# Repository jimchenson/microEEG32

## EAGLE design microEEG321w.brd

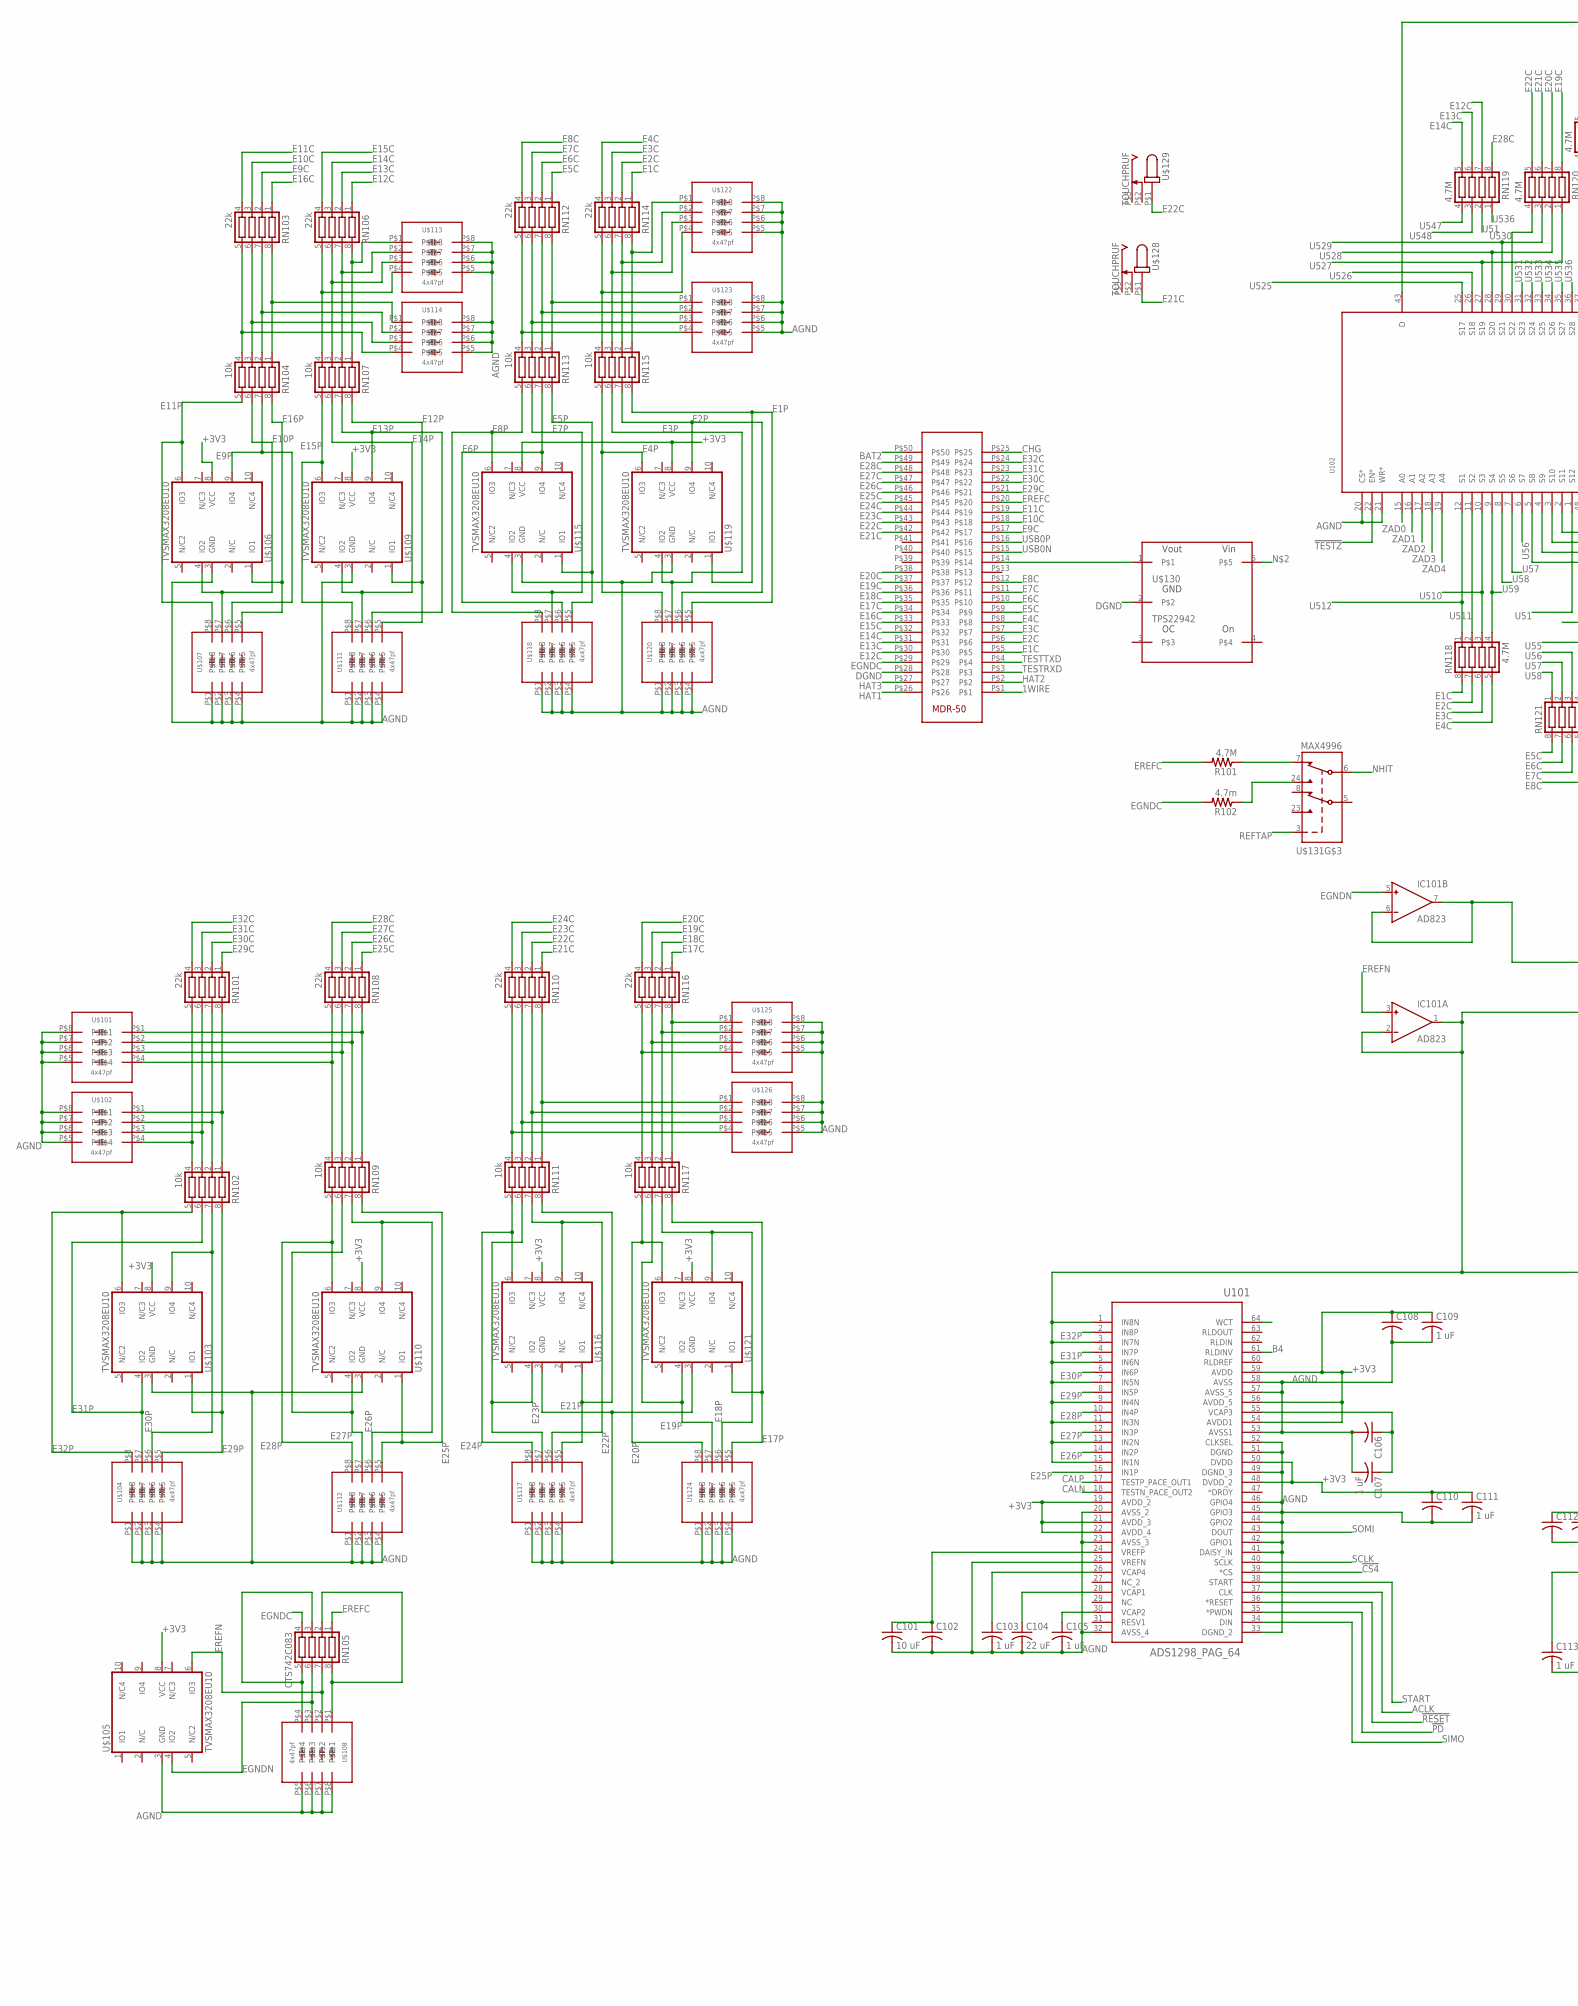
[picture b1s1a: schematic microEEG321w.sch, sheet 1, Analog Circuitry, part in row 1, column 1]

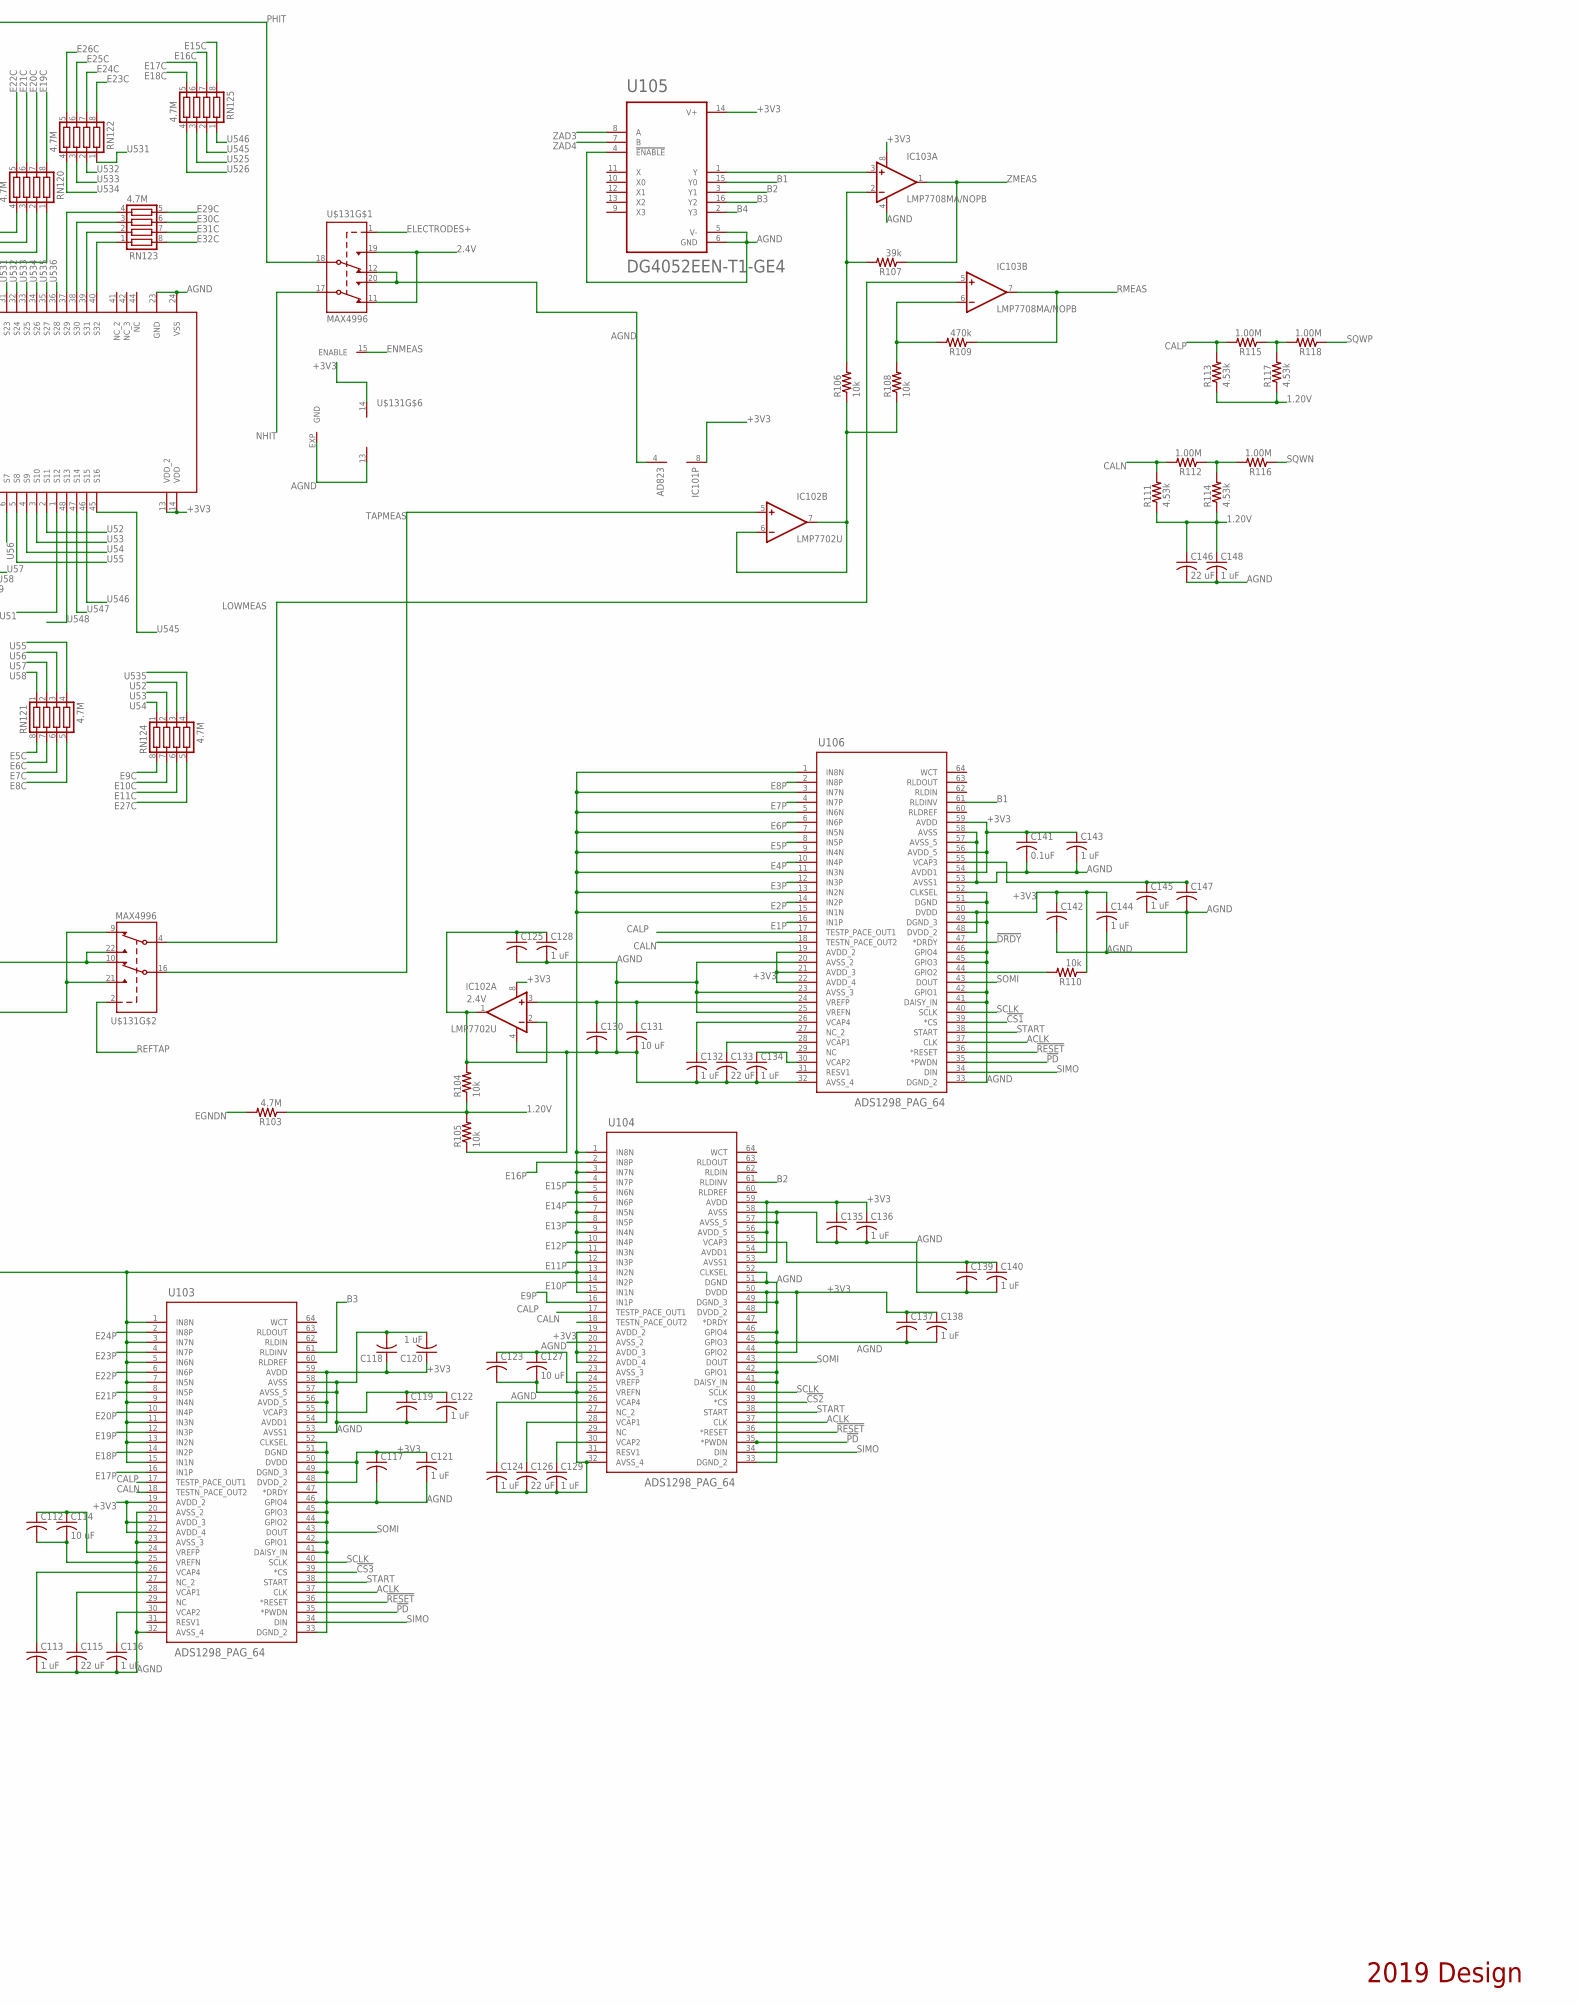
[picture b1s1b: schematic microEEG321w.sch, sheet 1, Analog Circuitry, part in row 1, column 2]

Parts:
C101, C114, C127: 10 uF; C0402K
C102, C106, C108, C110, C112, C117, C118, C119, C123, C125, C130, C135, C137, C139, C142, C147: C-USC0402K; C0402K
C103, C105, C107, C109, C111, C113, C116, C120, C121, C122, C124, C128, C129, C132, C134, C136, C138, C140, C143, C144, C145: 1 uF; C0402K
C104: 22 uF; C0603K
C115, C126, C133, C146: 22 uF; C0603
C131: 10 uF; C0805
C141: 0.1uF; C0402K
C148: 1 uF; C0402
IC101: AD823; MSOP08
IC102: LMP7702U; SO08
IC103: LMP7708MA/NOPB; SO08
R101, R103: 4.7M; R0402
R102: 4.7m; R0402
R104, R105, R106, R108, R110: 10k; R0402
R107: 39k; R0805
R109: 470k; R0805
R111, R113, R114, R117: 4.53k; R0805
R112, R115, R116, R118: 1.00M; R0402
RN101, RN103, RN106, RN108, RN110, RN112, RN114, RN116: 22k; CTS742C083
RN102, RN104, RN107, RN109, RN111, RN113, RN115, RN117: 10k; CTS742C083
RN105: CTS742C083
RN118, RN119, RN120, RN121, RN122, RN123, RN124, RN125: 4.7M; CTS742C083
U101, U103, U104, U106: ADS1298_PAG_64; PAG64
U102: ADG732BSUZ; SU_48
U105: DG4052EEN-T1-GE4; QFN40P260X180X60-16N
U$101, U$102, U$104, U$107, U$108, U$111, U$112, U$113, U$114, U$117, U$118, U$120, U$122, U$123, U$124, U$125, U$126: 4x47pf; CAP0508X4
U$103, U$105, U$106, U$109, U$110, U$115, U$116, U$119, U$121: TVSMAX3208EU10; UMAX10
U$127: PNLRECEPT; THROUGHHOLERECEPT
U$128, U$129: TOUCHPRUF; TOUCHPROOF
U$130: TPS22942; DCK
U$131: MAX4996; TQFN24-EP

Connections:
1.20V: C146.1, C148.1, R103.1, R104.1, R105.2, R111.1, R113.1, R114.1, R117.1
1WIRE: U$127.P$1; also elsewhere on the board
2.4V: C125.1, C128.1, IC102.1 (OUT), IC102.2 (-IN), R104.2, U$131.11 (NC2), U$131.19 (NO1); also elsewhere on the board
!CS1!: U106.39 (*CS); also elsewhere on the board
!CS2!: U104.39 (*CS); also elsewhere on the board
!CS3!: U103.39 (*CS); also elsewhere on the board
!CS4!: U101.39 (*CS); also elsewhere on the board
!DRDY!: U106.47 (*DRDY); also elsewhere on the board
!PD!: U101.35 (*PWDN), U103.35 (*PWDN), U104.35 (*PWDN), U106.35 (*PWDN); also elsewhere on the board
!RESET!: U101.36 (*RESET), U103.36 (*RESET), U104.36 (*RESET), U106.36 (*RESET); also elsewhere on the board
!TESTZ!: U102.22 (EN*); also elsewhere on the board
+3V3: C108.1, C109.1, C110.1, C111.1, C117.1, C118.1, C120.1, C121.1, C135.1, C136.1, C137.1, C138.1, C141.1, C142.1, C143.1, C144.1, IC101.8 (V+), IC102.8 (V+), IC103.8 (V+), R110.1, U101.19 (AVDD_2), U101.21 (AVDD_3), U101.22 (AVDD_4), U101.48 (DVDD_2), U101.50 (DVDD), U101.54 (AVDD1), U101.56 (AVDD_5), U101.59 (AVDD), U102.13 (VDD_2), U102.14 (VDD), U103.19 (AVDD_2), U103.21 (AVDD_3), U103.22 (AVDD_4), U103.48 (DVDD_2), U103.50 (DVDD), U103.54 (AVDD1), U103.56 (AVDD_5), U103.59 (AVDD), U104.19 (AVDD_2), U104.21 (AVDD_3), U104.22 (AVDD_4), U104.44 (GPIO2), U104.48 (DVDD_2), U104.50 (DVDD), U104.54 (AVDD1), U104.56 (AVDD_5), U104.59 (AVDD), U105.14 (V+), U106.19 (AVDD_2), U106.21 (AVDD_3), U106.22 (AVDD_4), U106.48 (DVDD_2), U106.50 (DVDD), U106.54 (AVDD1), U106.56 (AVDD_5), U106.59 (AVDD), U$103.8 (VCC), U$105.8 (VCC), U$106.8 (VCC), U$109.8 (VCC), U$110.8 (VCC), U$115.8 (VCC), U$116.8 (VCC), U$119.8 (VCC), U$121.8 (VCC), U$131.14 (V+); also elsewhere on the board
ACLK: U101.37 (CLK), U103.37 (CLK), U104.37 (CLK), U106.37 (CLK); also elsewhere on the board
AGND: C101.2, C102.2, C103.2, C104.2, C105.2, C106.2, C107.2, C108.2, C109.2, C110.2, C111.2, C112.2, C113.2, C114.2, C115.2, C116.2, C117.2, C118.2, C119.2, C120.2, C121.2, C122.2, C123.2, C124.2, C125.2, C126.2, C127.2, C128.2, C129.2, C130.2, C131.2, C132.2, C133.2, C134.2, C135.2, C136.2, C137.2, C138.2, C139.2, C140.2, C141.2, C142.2, C143.2, C144.2, C145.2, C146.2, C147.2, C148.2, IC101.4 (V-), IC102.4 (V-), IC103.4 (V-), R105.1, U101.20 (AVSS_2), U101.23 (AVSS_3), U101.25 (VREFN), U101.32 (AVSS_4), U101.33 (DGND_2), U101.41 (DAISY_IN), U101.42 (GPIO1), U101.44 (GPIO2), U101.45 (GPIO3), U101.46 (GPIO4), U101.49 (DGND_3), U101.51 (DGND), U101.52 (CLKSEL), U101.53 (AVSS1), U101.57 (AVSS_5), U101.58 (AVSS), U102.20 (CS*), U102.21 (WR*), U102.23 (GND), U102.24 (VSS), U103.20 (AVSS_2), U103.23 (AVSS_3), U103.25 (VREFN), U103.32 (AVSS_4), U103.33 (DGND_2), U103.41 (DAISY_IN), U103.42 (GPIO1), U103.44 (GPIO2), U103.45 (GPIO3), U103.46 (GPIO4), U103.49 (DGND_3), U103.51 (DGND), U103.52 (CLKSEL), U103.53 (AVSS1), U103.57 (AVSS_5), U103.58 (AVSS), U104.20 (AVSS_2), U104.23 (AVSS_3), U104.25 (VREFN), U104.32 (AVSS_4), U104.33 (DGND_2), U104.41 (DAISY_IN), U104.42 (GPIO1), U104.45 (GPIO3), U104.46 (GPIO4), U104.49 (DGND_3), U104.51 (DGND), U104.52 (CLKSEL), U104.53 (AVSS1), U104.57 (AVSS_5), U104.58 (AVSS), U105.4 (!ENABLE), U105.5 (V-), U105.6 (GND), U106.20 (AVSS_2), U106.23 (AVSS_3), U106.25 (VREFN), U106.32 (AVSS_4), U106.33 (DGND_2), U106.41 (DAISY_IN), U106.42 (GPIO1), U106.45 (GPIO3), U106.46 (GPIO4), U106.49 (DGND_3), U106.51 (DGND), U106.52 (CLKSEL), U106.53 (AVSS1), U106.57 (AVSS_5), U106.58 (AVSS), U$101.P$5, U$101.P$6, U$101.P$7, U$101.P$8, U$102.P$5, U$102.P$6, U$102.P$7, U$102.P$8, U$103.3 (GND), U$104.P$1, U$104.P$2, U$104.P$3, U$104.P$4, U$105.3 (GND), U$106.3 (GND), U$107.P$1, U$107.P$2, U$107.P$3, U$107.P$4, U$108.P$5, U$108.P$6, U$108.P$7, U$108.P$8, U$109.3 (GND), U$110.3 (GND), U$111.P$1, U$111.P$2, U$111.P$3, U$111.P$4, U$112.P$1, U$112.P$2, U$112.P$3, U$112.P$4, U$113.P$5, U$113.P$6, U$113.P$7, U$113.P$8, U$114.P$5, U$114.P$6, U$114.P$7, U$114.P$8, U$115.3 (GND), U$116.3 (GND), U$117.P$1, U$117.P$2, U$117.P$3, U$117.P$4, U$118.P$1, U$118.P$2, U$118.P$3, U$118.P$4, U$119.3 (GND), U$120.P$1, U$120.P$2, U$120.P$3, U$120.P$4, U$121.3 (GND), U$122.P$5, U$122.P$6, U$122.P$7, U$122.P$8, U$123.P$5, U$123.P$6, U$123.P$7, U$123.P$8, U$124.P$1, U$124.P$2, U$124.P$3, U$124.P$4, U$125.P$5, U$125.P$6, U$125.P$7, U$125.P$8, U$126.P$5, U$126.P$6, U$126.P$7, U$126.P$8, U$131.12 (NC1), U$131.13 (V-), U$131.20 (NO2), U$131.EXP (GND); also elsewhere on the board
B1: U105.15 (Y0), U106.61 (RLDINV)
B2: U104.61 (RLDINV), U105.3 (Y1)
B3: U103.61 (RLDINV), U105.16 (Y2)
B4: U101.61 (RLDINV), U105.2 (Y3)
BAT2: U$127.P$50; also elsewhere on the board
CALN: R111.2, R112.2, U101.18 (TESTN_PACE_OUT2), U103.18 (TESTN_PACE_OUT2), U104.18 (TESTN_PACE_OUT2), U106.18 (TESTN_PACE_OUT2)
CALP: R113.2, R115.2, U101.17 (TESTP_PACE_OUT1), U103.17 (TESTP_PACE_OUT1), U104.17 (TESTP_PACE_OUT1), U106.17 (TESTP_PACE_OUT1)
CHG: U$127.P$25; also elsewhere on the board
DGND: U$127.P$28, U$130.2; also elsewhere on the board
E1C: RN114.1, RN118.8, U$127.P$5
E1P: RN115.8, U106.16 (IN1P), U$119.1 (IO1), U$120.P$5
E2C: RN114.2, RN118.7, U$127.P$6
E2P: RN115.7, U106.14 (IN2P), U$119.9 (IO4), U$120.P$6
E3C: RN114.3, RN118.6, U$127.P$7
E3P: RN115.6, U106.12 (IN3P), U$119.4 (IO2), U$120.P$7
E4C: RN114.4, RN118.5, U$127.P$8
E4P: RN115.5, U106.10 (IN4P), U$119.6 (IO3), U$120.P$8
E5C: RN112.1, RN121.8, U$127.P$9
E5P: RN113.8, U106.8 (IN5P), U$115.1 (IO1), U$118.P$5
E6C: RN112.2, RN121.7, U$127.P$10
E6P: RN113.7, U106.6 (IN6P), U$115.9 (IO4), U$118.P$6
E7C: RN112.3, RN121.6, U$127.P$11
E7P: RN113.6, U106.4 (IN7P), U$115.4 (IO2), U$118.P$7
E8C: RN112.4, RN121.5, U$127.P$12
E8P: RN113.5, U106.2 (IN8P), U$115.6 (IO3), U$118.P$8
E9C: RN103.2, RN124.8, U$127.P$17
E9P: RN104.7, U104.16 (IN1P), U$106.9 (IO4), U$107.P$6
E10C: RN103.3, RN124.7, U$127.P$18
E10P: RN104.6, U104.14 (IN2P), U$106.4 (IO2), U$107.P$7
E11C: RN103.4, RN124.6, U$127.P$19
E11P: RN104.5, U104.12 (IN3P), U$106.6 (IO3), U$107.P$8
E12C: RN106.1, RN119.7, U$127.P$30
E12P: RN107.8, U104.10 (IN4P), U$109.1 (IO1), U$111.P$5
E13C: RN106.2, RN119.6, U$127.P$31
E13P: RN107.7, U104.8 (IN5P), U$109.9 (IO4), U$111.P$6
E14C: RN106.3, RN119.5, U$127.P$32
E14P: RN107.6, U104.6 (IN6P), U$109.4 (IO2), U$111.P$7
E15C: RN106.4, RN125.8, U$127.P$33
E15P: RN107.5, U104.4 (IN7P), U$109.6 (IO3), U$111.P$8
E16C: RN103.1, RN125.7, U$127.P$34
E16P: RN104.8, U104.2 (IN8P), U$106.1 (IO1), U$107.P$5
E17C: RN116.1, RN125.6, U$127.P$35
E17P: RN117.8, U103.16 (IN1P), U$121.1 (IO1), U$124.P$5
E18C: RN116.2, RN125.5, U$127.P$36
E18P: RN117.7, U103.14 (IN2P), U$121.9 (IO4), U$124.P$6
E19C: RN116.3, RN120.8, U$127.P$37
E19P: RN117.6, U103.12 (IN3P), U$121.4 (IO2), U$124.P$7
E20C: RN116.4, RN120.7, U$127.P$38
E20P: RN117.5, U103.10 (IN4P), U$121.6 (IO3), U$124.P$8
E21C: RN110.1, RN120.6, U$127.P$42, U$128.P$1 (3)
E21P: RN111.8, U103.8 (IN5P), U$116.1 (IO1), U$117.P$5
E22C: RN110.2, RN120.5, U$127.P$43, U$129.P$1 (3)
E22P: RN111.7, U103.6 (IN6P), U$116.9 (IO4), U$117.P$6
E23C: RN110.3, RN122.8, U$127.P$44
E23P: RN111.6, U103.4 (IN7P), U$116.4 (IO2), U$117.P$7
E24C: RN110.4, RN122.7, U$127.P$45
E24P: RN111.5, U103.2 (IN8P), U$116.6 (IO3), U$117.P$8
E25C: RN108.1, RN122.6, U$127.P$46
E25P: RN109.8, U101.16 (IN1P), U$110.1 (IO1), U$112.P$5
E26C: RN108.2, RN122.5, U$127.P$47
E26P: RN109.7, U101.14 (IN2P), U$110.9 (IO4), U$112.P$6
E27C: RN108.3, RN124.5, U$127.P$48
E27P: RN109.6, U101.12 (IN3P), U$110.4 (IO2), U$112.P$7
E28C: RN108.4, RN119.8, U$127.P$49
E28P: RN109.5, U101.10 (IN4P), U$110.6 (IO3), U$112.P$8
E29C: RN101.1, RN123.5, U$127.P$21
E29P: RN102.8, U101.8 (IN5P), U$103.1 (IO1), U$104.P$5
E30C: RN101.2, RN123.6, U$127.P$22
E30P: RN102.7, U101.6 (IN6P), U$103.9 (IO4), U$104.P$6
E31C: RN101.3, RN123.7, U$127.P$23
E31P: RN102.6, U101.4 (IN7P), U$103.4 (IO2), U$104.P$7
E32C: RN101.4, RN123.8, U$127.P$24
E32P: RN102.5, U101.2 (IN8P), U$103.6 (IO3), U$104.P$8
EGNDC: R102.2, RN105.4, U$127.P$29
EGNDN: IC101.5 (IN+), R103.2, RN105.6, U$105.4 (IO2), U$108.P$3
ELECTRODES+: U$131.1 (CB); also elsewhere on the board
ENMEAS: U$131.15 (ENABLE); also elsewhere on the board
EREFC: R101.2, RN105.1, U$127.P$20
EREFN: IC101.3 (IN+), RN105.7, U$105.6 (IO3), U$108.P$2
HAT1: U$127.P$26; also elsewhere on the board
HAT2: U$127.P$2; also elsewhere on the board
HAT3: U$127.P$27; also elsewhere on the board
LOWMEAS: IC103.5 (+IN), U$131.4 (COM2)
unnamed: R110.2, U106.44 (GPIO2)
unnamed 116: U$130.5; also elsewhere on the board
unnamed: R101.1, U$131.7 (NC2)
unnamed: IC103.3 (+IN), U105.1 (Y)
unnamed: R102.1, U$131.24 (NO2)
unnamed: RN112.5, RN113.4, U$123.P$4
unnamed: IC101.6 (IN-), IC101.7 (OUT), U$131.10 (NC1), U$131.22 (NO2)
unnamed: RN123.4, U102.37 (S29)
unnamed: RN112.6, RN113.3, U$123.P$3
unnamed: RN112.7, RN113.2, U$123.P$2
unnamed: RN123.3, U102.38 (S30)
unnamed: RN123.2, U102.39 (S31)
unnamed: RN123.1, U102.40 (S32)
unnamed: RN112.8, RN113.1, U$123.P$1
unnamed: RN105.2, RN105.8, U$108.P$1
unnamed: RN106.8, RN107.1, U$113.P$1
unnamed: RN106.7, RN107.2, U$113.P$2
unnamed: RN106.6, RN107.3, U$113.P$3
unnamed: RN106.5, RN107.4, U$113.P$4
unnamed: RN103.8, RN104.1, U$114.P$1
unnamed: RN114.8, RN115.1, U$122.P$1
unnamed: RN114.7, RN115.2, U$122.P$2
unnamed: RN114.6, RN115.3, U$122.P$3
unnamed: RN114.5, RN115.4, U$122.P$4
unnamed: RN103.7, RN104.2, U$114.P$2
unnamed: RN103.6, RN104.3, U$114.P$3
unnamed: RN103.5, RN104.4, U$114.P$4
unnamed: C130.1, C131.1, IC102.3 (+IN), U106.24 (VREFP)
unnamed: RN116.8, RN117.1, U$125.P$1
unnamed: RN116.7, RN117.2, U$125.P$2
unnamed: RN116.6, RN117.3, U$125.P$3
unnamed: RN116.5, RN117.4, U$125.P$4
unnamed: IC102.6 (-IN), IC102.7 (OUT), R106.1, R108.1
unnamed: IC103.6 (-IN), R108.2, R109.2
unnamed: IC103.2 (-IN), R106.2, R107.2
unnamed: RN101.5, RN102.4, U$102.P$4
unnamed: C105.1, U101.30 (VCAP2)
unnamed: C145.1, C147.1, U106.55 (VCAP3)
unnamed: C101.1, C102.1, U101.24 (VREFP)
unnamed: RN110.8, RN111.1, U$126.P$1
unnamed: RN110.7, RN111.2, U$126.P$2
unnamed: RN110.6, RN111.3, U$126.P$3
unnamed: C104.1, U101.28 (VCAP1)
unnamed: C106.1, C107.1, U101.55 (VCAP3)
unnamed: C103.1, U101.26 (VCAP4)
unnamed: C116.1, U103.30 (VCAP2)
unnamed: C115.1, U103.28 (VCAP1)
unnamed: C113.1, U103.26 (VCAP4)
unnamed: C123.1, C127.1, U104.24 (VREFP)
unnamed: C129.1, U104.30 (VCAP2)
unnamed: C126.1, U104.28 (VCAP1)
unnamed: C124.1, U104.26 (VCAP4)
unnamed: C134.1, U106.30 (VCAP2)
unnamed: C133.1, U106.28 (VCAP1)
unnamed: C132.1, U106.26 (VCAP4)
unnamed: RN110.5, RN111.4, U$126.P$4
unnamed: RN101.6, RN102.3, U$102.P$3
unnamed: RN101.7, RN102.2, U$102.P$2
unnamed: RN101.8, RN102.1, U$102.P$1
unnamed: RN108.5, RN109.4, U$101.P$4
unnamed: RN108.6, RN109.3, U$101.P$3
unnamed: RN108.7, RN109.2, U$101.P$2
unnamed: RN108.8, RN109.1, U$101.P$1
unnamed: R115.1, R117.2, R118.2
unnamed: R112.1, R114.2, R116.2
unnamed: C139.1, C140.1, U104.55 (VCAP3)
unnamed: U$127.P$14, U$130.1
unnamed: C112.1, C114.1, U103.24 (VREFP)
unnamed: C119.1, C122.1, U103.55 (VCAP3)
unnamed: RN105.3, RN105.5, U$108.P$4
NCOMM: IC101.1 (OUT), IC101.2 (IN-), U101.1 (IN8N), U101.3 (IN7N), U101.5 (IN6N), U101.7 (IN5N), U101.9 (IN4N), U101.11 (IN3N), U101.13 (IN2N), U101.15 (IN1N), U103.1 (IN8N), U103.3 (IN7N), U103.5 (IN6N), U103.7 (IN5N), U103.9 (IN4N), U103.11 (IN3N), U103.13 (IN2N), U103.15 (IN1N), U104.1 (IN8N), U104.3 (IN7N), U104.5 (IN6N), U104.7 (IN5N), U104.9 (IN4N), U104.11 (IN3N), U104.13 (IN2N), U104.15 (IN1N), U106.1 (IN8N), U106.3 (IN7N), U106.5 (IN6N), U106.7 (IN5N), U106.9 (IN4N), U106.11 (IN3N), U106.13 (IN2N), U106.15 (IN1N), U$131.9 (NC2), U$131.21 (NO1)
NHIT: U$131.6 (COM2), U$131.17 (COM2)
PHIT: U102.43 (D), U$131.18 (COM1)
REFTAP: U$131.2 (CB), U$131.3 (CB); also elsewhere on the board
RMEAS: IC103.7 (OUT), R109.1; also elsewhere on the board
SCLK: U101.40 (SCLK), U103.40 (SCLK), U104.40 (SCLK), U106.40 (SCLK); also elsewhere on the board
SIMO: U101.34 (DIN), U103.34 (DIN), U104.34 (DIN), U106.34 (DIN); also elsewhere on the board
SOMI: U101.43 (DOUT), U103.43 (DOUT), U104.43 (DOUT), U106.43 (DOUT); also elsewhere on the board
SQWN: R116.1; also elsewhere on the board
SQWP: R118.1; also elsewhere on the board
START: U101.38 (START), U103.38 (START), U104.38 (START), U106.38 (START); also elsewhere on the board
TAPMEAS: IC102.5 (+IN), U$131.16 (COM1)
TESTRXD: U$127.P$3; also elsewhere on the board
TESTTXD: U$127.P$4; also elsewhere on the board
U51: RN119.2, U102.1 (S12)
U52: RN124.3, U102.2 (S11)
U53: RN124.2, U102.3 (S10)
U54: RN124.1, U102.4 (S9)
U55: RN121.4, U102.5 (S8)
U56: RN121.3, U102.6 (S7)
U57: RN121.2, U102.7 (S6)
U58: RN121.1, U102.8 (S5)
U59: RN118.4, U102.9 (S4)
U510: RN118.3, U102.10 (S3)
U511: RN118.2, U102.11 (S2)
U512: RN118.1, U102.12 (S1)
U525: RN125.3, U102.25 (S17)
U526: RN125.4, U102.26 (S18)
U527: RN120.1, U102.27 (S19)
U528: RN120.2, U102.28 (S20)
U529: RN120.3, U102.29 (S21)
U530: RN120.4, U102.30 (S22)
U531: RN122.1, U102.31 (S23)
U532: RN122.2, U102.32 (S24)
U533: RN122.3, U102.33 (S25)
U534: RN122.4, U102.34 (S26)
U535: RN124.4, U102.35 (S27)
U536: RN119.1, U102.36 (S28)
U545: RN125.2, U102.45 (S16)
U546: RN125.1, U102.46 (S15)
U547: RN119.4, U102.47 (S14)
U548: RN119.3, U102.48 (S13)
USB0N: U$127.P$15; also elsewhere on the board
USB0P: U$127.P$16; also elsewhere on the board
WCT: U101.64 (WCT)
ZAD0: U102.15 (A0); also elsewhere on the board
ZAD1: U102.16 (A1); also elsewhere on the board
ZAD2: U102.17 (A2); also elsewhere on the board
ZAD3: U102.18 (A3), U105.8 (A); also elsewhere on the board
ZAD4: U102.19 (A4), U105.7 (B); also elsewhere on the board
ZMEAS: IC103.1 (OUT), R107.1; also elsewhere on the board

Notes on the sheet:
2019 Design

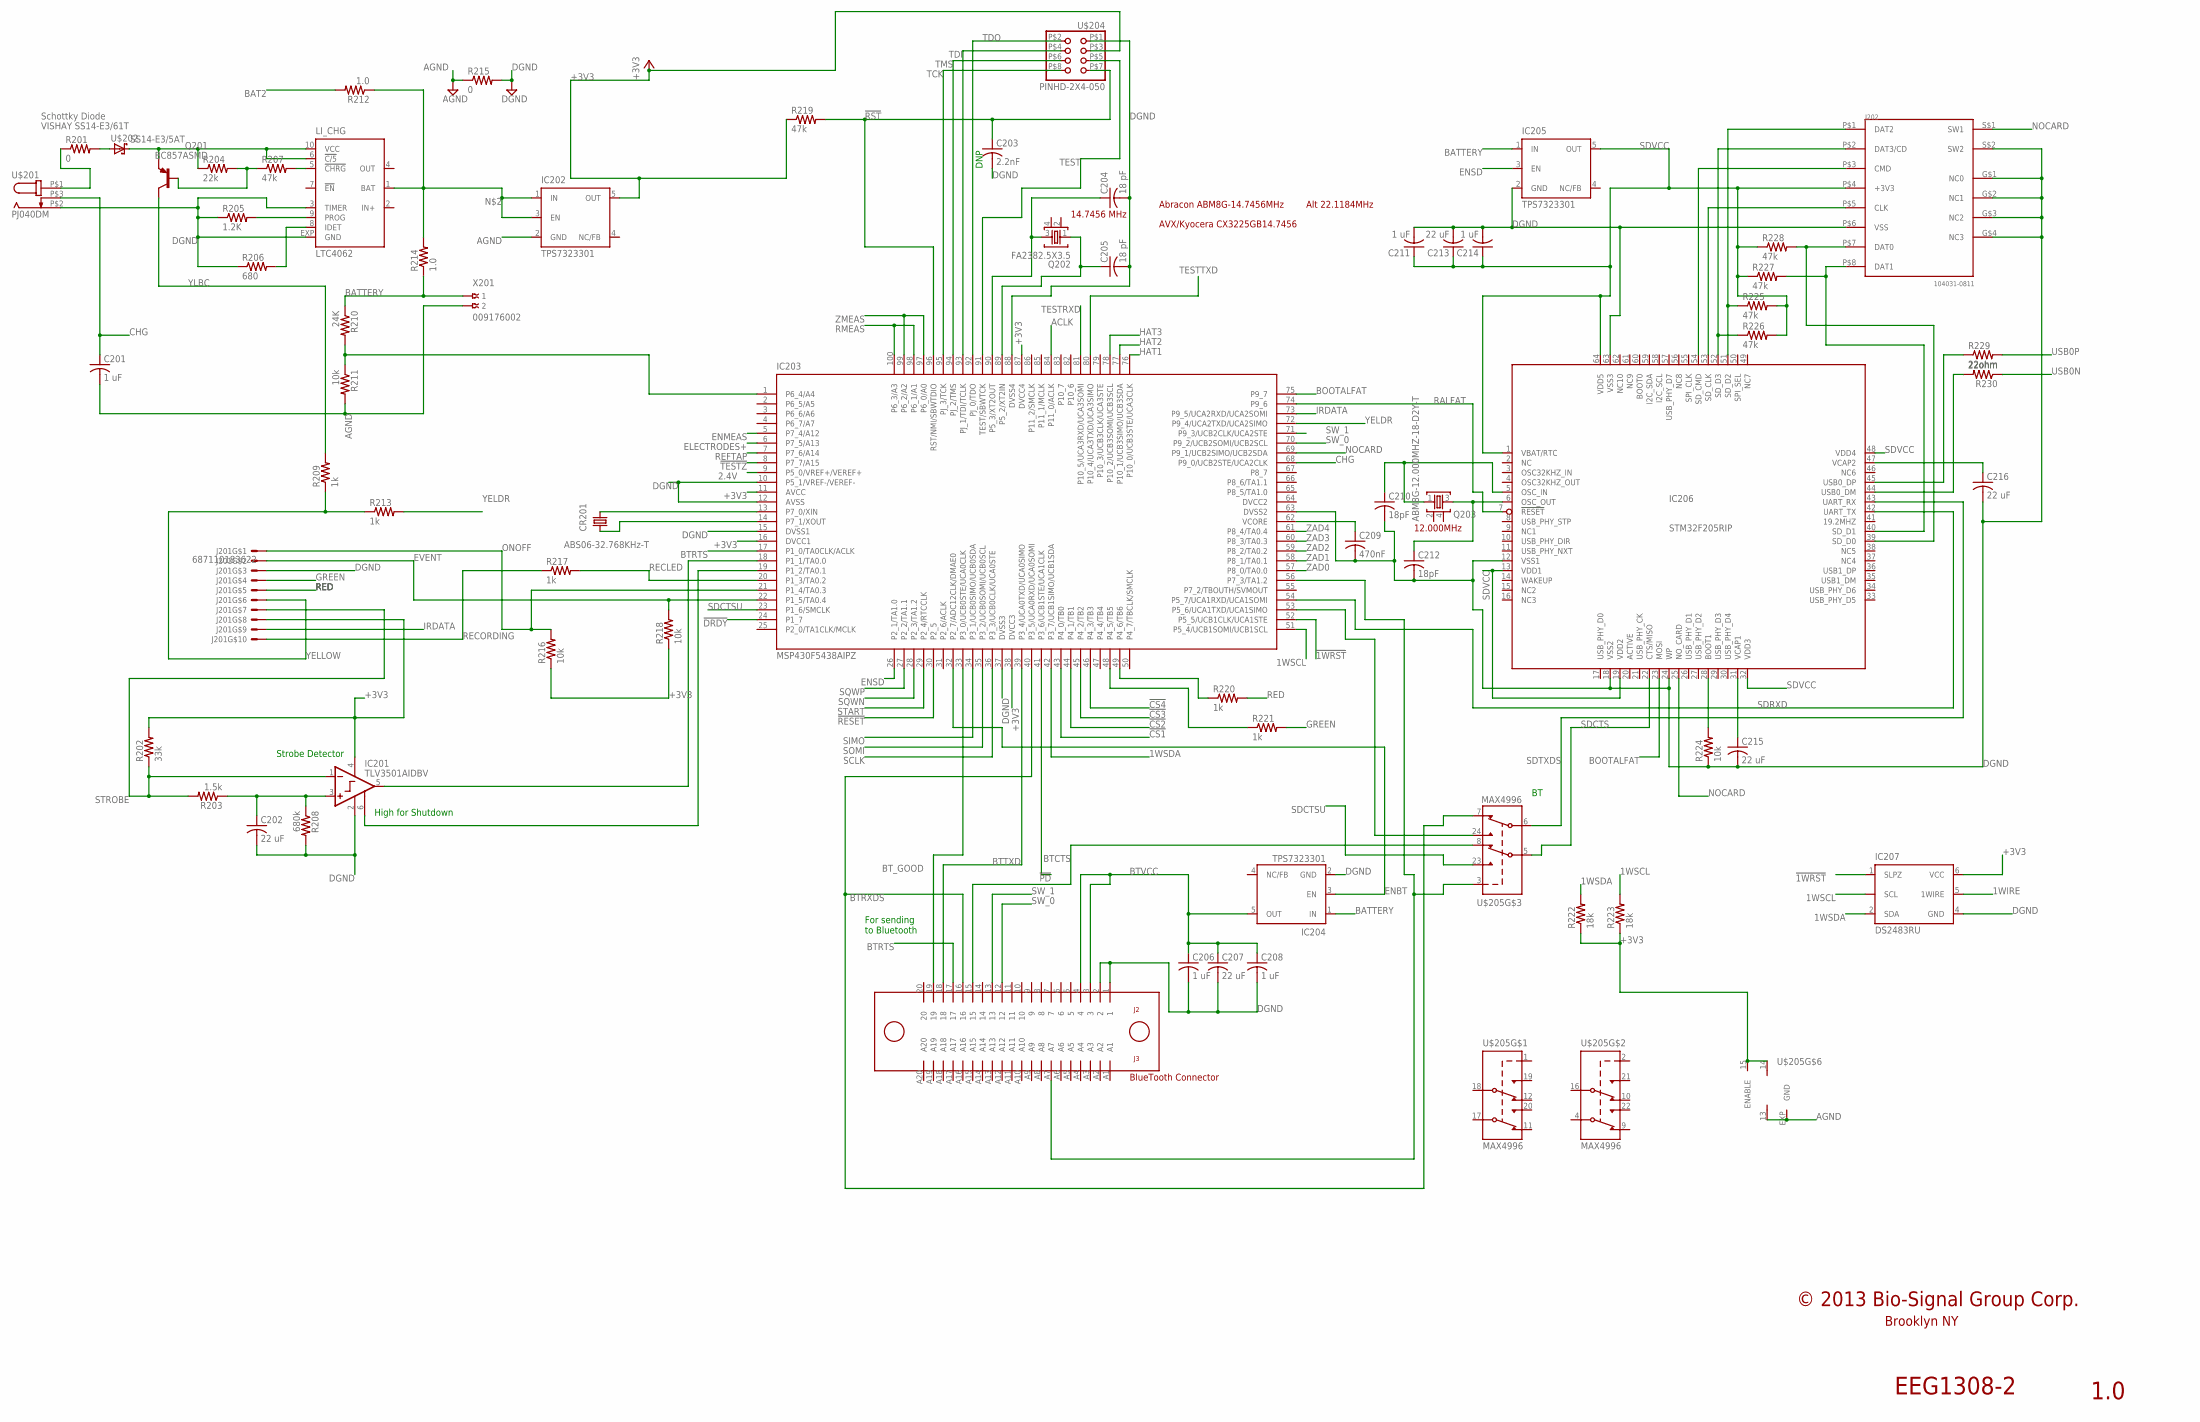
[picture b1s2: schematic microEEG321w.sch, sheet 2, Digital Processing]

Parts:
C201, C206, C208, C211, C214: 1 uF; C0402K
C202, C207, C213, C215: 22 uF; C0603K
C203: 2.2nF; C0603
C204, C205: 18 pF; C0603
C209: 470nF; C0402
C210, C212: 18pF; C0402K
C216: 22 uF; C0603
CR201: ABS06-32.768KHz-T; FC-12M
IC201: TLV3501AIDBV; SOT23-6
IC202, IC204, IC205: TPS7323301; SOT23-DBV
IC203: MSP430F5438AIPZ; PZ_S-PQFP-G100
IC206: STM32F205RIP; SQFP-S-10X10-64
IC207: DS2483RU; SOT23-6L
J201: 687110183622; XF2L-1025-1
J202: 104031-0811; MOLEX_SD
LI_CHG: LTC4062; DFN10-3X3
Q201: BC857ASMD; SOT23-BEC
Q202: FA2382.5X3.5; FA238V
Q203: ABM8G-12.000MHZ-18-D2Y-T; FA238V
R201, R215: 0; R0402
R202: 33k; R0402
R203: 1.5k; R0402
R204: 22k; R0805
R205: 1.2K; R0805
R206: 680; R0805
R207, R219, R225, R226, R227, R228: 47k; R0402
R208: 680k; R0402
R209, R213, R217, R220, R221: 1k; R0402
R210: 24K; R0805
R211, R216, R218, R224: 10k; R0402
R212, R214: 1.0; R0402
R222, R223: 18k; R0805
R229, R230: 22ohm; R0402
U$201: PJ040DM; PJ040
U$202: SS14-E3/5AT; DO214AC
U$203: FSI-140-03-G-D-M-AD-TR; FSI-110-03-X-D-E-AD
U$204: PINHD-2X4-050; 2X04/90-050
U$205: MAX4996; TQFN24-EP
X201: 009176002

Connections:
1WIRE: IC207.5 (1WIRE); also elsewhere on the board
1WSCL: IC203.51 (P5_4/UCB1SOMI/UCB1SCL), IC207.3 (SCL), R223.2
1WSDA: IC203.42 (P3_7/UCB1SIMO/UCB1SDA), IC207.2 (SDA), R222.2
2.4V: IC203.9 (P5_0/VREF+/VEREF+); also elsewhere on the board
!1WRST!: IC203.52 (P5_5/UCB1CLK/UCA1STE), IC207.1 (SLPZ)
!CS1!: IC203.43 (P4_0/TB0); also elsewhere on the board
!CS2!: IC203.44 (P4_1/TB1); also elsewhere on the board
!CS3!: IC203.45 (P4_2/TB2); also elsewhere on the board
!CS4!: IC203.46 (P4_3/TB3); also elsewhere on the board
!DRDY!: IC203.24 (P1_7); also elsewhere on the board
!PD!: IC203.41 (P3_6/UCB1STE/UCA1CLK); also elsewhere on the board
!RESET!: IC203.30 (P2_5); also elsewhere on the board
!RST!: C203.1, IC203.96 (RST/NMI/SBWTDIO), R219.2, U$204.P$7 (7)
!TESTZ!: IC203.8 (P7_7/A15); also elsewhere on the board
+3V3: IC201.4 (V+), IC202.5 (OUT), IC203.11 (AVCC), IC203.16 (DVCC1), IC203.38 (DVCC3), IC203.87 (DVCC4), IC207.6 (VCC), J201.8 (MS), R202.2, R216.1, R218.1, R219.1, R222.1, R223.1, U$204.P$3 (3), U$205.14 (V+), U$205.15 (ENABLE); also elsewhere on the board
ACLK: IC203.84 (P11_0/ACLK); also elsewhere on the board
AGND: C201.2, IC202.2 (GND), R211.2, R215.1, U$205.13 (V-), U$205.EXP (GND), X201.2; also elsewhere on the board
BAT2: R212.2; also elsewhere on the board
BATTERY: IC204.1 (IN), IC205.1 (IN), R210.1, R214.1, X201.1
BOOTALFAT: IC203.75 (P9_7), IC206.23 (MOSI)
BTCTS: U$203.15, U$205.8 (NC1)
BTRTS: IC203.17 (P1_0/TA0CLK/ACLK), U$203.17
BTRXDS: IC203.40 (P3_5/UCA0RXD/UCA0SOMI), U$203.16, U$205.7 (NC2)
BTTXD: IC203.39 (P3_4/UCA0TXD/UCA0SIMO), U$203.18
BTVCC: C206.1, C207.1, C208.1, IC204.5 (OUT), U$203.3, U$203.4
BT_GOOD: IC203.33 (P3_0/UCB0STE/UCA0CLK), U$203.19
CHG: C201.1, IC203.68 (P9_0/UCB2STE/UCA2CLK), U$201.P$3 (2); also elsewhere on the board
DGND: C202.2, C203.2, C204.2, C205.2, C206.2, C207.2, C208.2, C209.2, C210.2, C211.2, C212.2, C213.2, C214.2, C215.2, C216.2, IC201.2 (V-), IC203.10 (P5_1/VREF-/VEREF-), IC203.12 (AVSS), IC203.15 (DVSS1), IC203.37 (DVSS3), IC203.63 (DVSS2), IC203.88 (DVSS4), IC204.2 (GND), IC205.2 (GND), IC206.12 (VSS1), IC206.18 (VSS2), IC206.24 (WP), IC206.63 (VSS3), IC207.4 (GND), J201.3 (MS), J202.G$1 (NC0), J202.G$2 (NC1), J202.G$3 (NC2), J202.G$4 (NC3), J202.P$6 (VSS), J202.S$2 (SW2), LI_CHG.3 (TIMER), LI_CHG.EXP (GND), R205.1, R206.1, R208.2, R215.2, R224.1, U$201.P$2 (1), U$203.1, U$203.2, U$204.P$1 (1); also elsewhere on the board
DVCC2: IC203.64 (DVCC2)
ELECTRODES+: IC203.6 (P7_5/A13); also elsewhere on the board
ENBT: IC203.32 (P2_7/ADC12CLK/DMAE0), IC204.3 (EN)
ENMEAS: IC203.5 (P7_4/A12); also elsewhere on the board
ENSD: IC203.26 (P2_1/TA1.0), IC205.3 (EN)
EVENT: IC203.22 (P1_5/TA0.4), J201.2 (MS), R218.2
GREEN: J201.4 (MS), R221.2
HAT1: IC203.76 (P10_0/UCB3STE/UCA3CLK); also elsewhere on the board
HAT2: IC203.77 (P10_1/UCB3SIMO/UCB3SDA); also elsewhere on the board
HAT3: IC203.78 (P10_2/UCB3SOMI/UCB3SCL); also elsewhere on the board
IRDATA: IC203.73 (P9_5/UCA2RXD/UCA2SOMI), J201.9 (MS)
unnamed 116: IC202.1 (IN), IC202.3 (EN), LI_CHG.1 (BAT), R212.1, R214.2; also elsewhere on the board
unnamed: R201.1, U$201.P$1 (3)
unnamed: R201.2, U$202.A
unnamed: IC201.5 (OUT), IC203.18 (P1_1/TA0.0)
unnamed: IC206.40 (SD_D1), J202.P$8 (DAT1), R227.2
unnamed: IC201.6 (SHDN), IC203.19 (P1_2/TA0.1)
unnamed: C202.1, IC201.3 (+IN), R203.1, R208.1
unnamed: Q201.B, R204.2, R207.1
unnamed: C209.1, IC203.62 (VCORE)
unnamed: IC203.48 (P4_5/TB5), R221.1
unnamed: IC206.28 (BOOT1), R224.2
unnamed: CR201.2, IC203.13 (P7_0/XIN)
unnamed: C212.1, IC206.6 (OSC_OUT), Q203.3
unnamed: CR201.1, IC203.14 (P7_1/XOUT)
unnamed: C210.1, IC206.5 (OSC_IN), Q203.1
unnamed: C216.1, IC206.47 (VCAP2)
unnamed: C215.1, IC206.31 (VCAP1)
unnamed: IC206.51 (SD_D2), J202.P$1 (DAT2), R225.1
unnamed: IC206.52 (SD_D3), J202.P$2 (DAT3/CD), R226.1
unnamed: IC206.54 (SD_CMD), J202.P$3 (CMD)
unnamed: LI_CHG.9 (PROG), R205.2
unnamed: IC206.53 (SD_CLK), J202.P$5 (CLK)
unnamed: IC206.39 (SD_D0), J202.P$7 (DAT0), R228.2
unnamed: LI_CHG.6 (!C/5), LI_CHG.10 (VCC), Q201.E, R204.1, U$202.C
unnamed: IC203.49 (P4_6/TB6), R220.1
unnamed: IC203.53 (P5_6/UCA1TXD/UCA1SIMO), U$205.24 (NO2)
unnamed: C205.1, IC203.89 (P5_2/XT2IN), Q202.1
unnamed: IC203.1 (P6_4/A4), R210.2, R211.1
unnamed: C204.1, IC203.90 (P5_3/XT2OUT), Q202.3
unnamed: IC203.56 (P7_3/TA1.2), U$203.A7, U$205.3 (CB)
unnamed: LI_CHG.5 (!CHRG), R207.2
unnamed: LI_CHG.8 (IDET), R206.2
unnamed: IC206.45 (USB0_DP), R229.1
unnamed: IC206.44 (USB0_DM), R230.2
NOCARD: IC203.69 (P9_1/UCB2SIMO/UCB2SDA), IC206.25 (NO_CARD), J202.S$1 (SW1)
ONOFF: IC203.21 (P1_4/TA0.3), J201.1 (MSV), R216.2
RALFAT: IC203.74 (P9_6), IC206.7 (!RESET!)
RECLED: IC203.20 (P1_3/TA0.2), R217.2
RECORDING: J201.10 (MS), R217.1
RED: J201.5 (MS), R220.2
REFTAP: IC203.7 (P7_6/A14); also elsewhere on the board
RMEAS: IC203.98 (P6_1/A1), IC203.100 (P6_3/A3); also elsewhere on the board
SCLK: IC203.36 (P3_3/UCB0CLK/UCA0STE); also elsewhere on the board
SDCTS: IC206.22 (CTS/MISO), U$205.5 (COM1)
SDCTSU: IC203.23 (P1_6/SMCLK), U$205.23 (NO1)
SDRXD: IC203.54 (P5_7/UCA1RXD/UCA1SOMI), IC206.42 (UART_TX)
SDTXDS: IC206.43 (UART_RX), U$205.6 (COM2)
SDVCC: C211.1, C213.1, C214.1, IC205.5 (OUT), IC206.1 (VBAT/RTC), IC206.13 (VDD1), IC206.19 (VDD2), IC206.32 (VDD3), IC206.48 (VDD4), IC206.64 (VDD5), J202.P$4 (+3V3), R225.2, R226.2, R227.1, R228.1
SIMO: IC203.34 (P3_1/UCB0SIMO/UCB0SDA); also elsewhere on the board
SOMI: IC203.35 (P3_2/UCB0SOMI/UCB0SCL); also elsewhere on the board
SQWN: IC203.28 (P2_3/TA1.2); also elsewhere on the board
SQWP: IC203.27 (P2_2/TA1.1); also elsewhere on the board
START: IC203.29 (P2_4/RTCCLK); also elsewhere on the board
STROBE: IC201.1 (-IN), J201.7 (MS), R202.1, R203.2
SW_0: IC203.70 (P9_2/UCB2SOMI/UCB2SCL), U$203.12
SW_1: IC203.71 (P9_3/UCB2CLK/UCA2STE), U$203.13
TCK: IC203.95 (PJ_3/TCK), U$204.P$8 (8)
TDI: IC203.93 (PJ_1/TDI/TCLK), U$204.P$4 (4)
TDO: IC203.92 (PJ_0/TDO), U$204.P$2 (2)
TEST: IC203.91 (TEST/SBWTCK), U$204.P$5 (5)
TESTRXD: IC203.81 (P10_5/UCA3RXD/UCA3SOMI); also elsewhere on the board
TESTTXD: IC203.80 (P10_4/UCA3TXD/UCA3SIMO); also elsewhere on the board
TMS: IC203.94 (PJ_2/TMS), U$204.P$6 (6)
USB0N: R230.1; also elsewhere on the board
USB0P: R229.2; also elsewhere on the board
YELDR: IC203.72 (P9_4/UCA2TXD/UCA2SIMO), R213.2
YELLOW: J201.6 (MS), R209.1, R213.1
YLBC: Q201.C, R209.2
ZAD0: IC203.57 (P8_0/TA0.0); also elsewhere on the board
ZAD1: IC203.58 (P8_1/TA0.1); also elsewhere on the board
ZAD2: IC203.59 (P8_2/TA0.2); also elsewhere on the board
ZAD3: IC203.60 (P8_3/TA0.3); also elsewhere on the board
ZAD4: IC203.61 (P8_4/TA0.4); also elsewhere on the board
ZMEAS: IC203.97 (P6_0/A0), IC203.99 (P6_2/A2); also elsewhere on the board

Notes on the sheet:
14.7456 MHz
Abracon ABM8G-14.7456MHz
AVX/Kyocera CX3225GB14.7456
Alt 22.1184MHz
BlueTooth Connector
12.000MHz
DNP
VISHAY SS14-E3/61T
Schottky Diode
EEG1308-2
1.0
© 2013 Bio-Signal Group Corp.
Brooklyn NY
High for Shutdown
Strobe Detector
For sending to Bluetooth

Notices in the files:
microEEG321w.brd:
microEEG32X © 2019 BioSignal Group Corp
